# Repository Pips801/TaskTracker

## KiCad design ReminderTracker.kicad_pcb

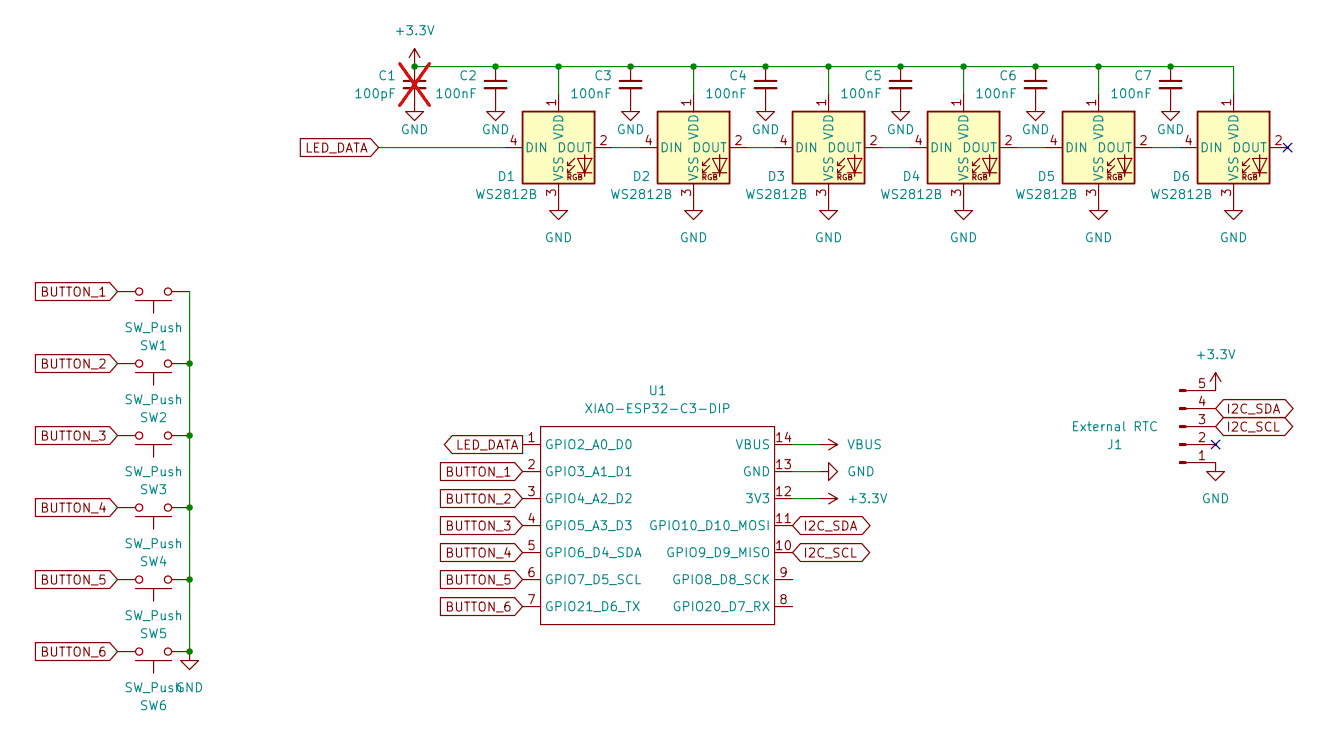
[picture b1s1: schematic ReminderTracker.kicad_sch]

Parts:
C1: 100pF; C_1206_3216Metric_Pad1.33x1.80mm_HandSolder; not fitted
C2, C3, C4, C5, C6, C7: 100nF; C_1206_3216Metric_Pad1.33x1.80mm_HandSolder
D1, D2, D3, D4, D5, D6: WS2812B; LED_WS2812B-Mini_PLCC4_3.5x3.5mm
J1: External RTC; PinHeader_1x05_P2.54mm_Vertical
SW1, SW2, SW3, SW4, SW5, SW6: SW_Push; SW_PUSH_6mm
U1: XIAO-ESP32-C3-DIP

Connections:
+3.3V: C1.1, C2.1, C3.1, C4.1, C5.1, C6.1, C7.1, D1.1 (VDD), D2.1 (VDD), D3.1 (VDD), D4.1 (VDD), D5.1 (VDD), D6.1 (VDD), J1.5, U1.12 (3V3)
BUTTON_1: SW1.2, U1.2 (GPIO3_A1_D1)
BUTTON_2: SW2.2, U1.3 (GPIO4_A2_D2)
BUTTON_3: SW3.2, U1.4 (GPIO5_A3_D3)
BUTTON_4: SW4.2, U1.5 (GPIO6_D4_SDA)
BUTTON_5: SW5.2, U1.6 (GPIO7_D5_SCL)
BUTTON_6: SW6.2, U1.7 (GPIO21_D6_TX)
GND: C1.2, C2.2, C3.2, C4.2, C5.2, C6.2, C7.2, D1.3 (VSS), D2.3 (VSS), D3.3 (VSS), D4.3 (VSS), D5.3 (VSS), D6.3 (VSS), J1.1, SW1.1, SW2.1, SW3.1, SW4.1, SW5.1, SW6.1, U1.13 (GND); also elsewhere on the board
I2C_SCL: J1.3, U1.10 (GPIO9_D9_MISO)
I2C_SDA: J1.4, U1.11 (GPIO10_D10_MOSI)
LED_DATA: D1.4 (DIN), U1.1 (GPIO2_A0_D0)
unnamed: D1.2 (DOUT), D2.4 (DIN)
unnamed: D2.2 (DOUT), D3.4 (DIN)
unnamed: D3.2 (DOUT), D4.4 (DIN)
unnamed: D4.2 (DOUT), D5.4 (DIN)
unnamed: D5.2 (DOUT), D6.4 (DIN)
VBUS: U1.14 (VBUS)

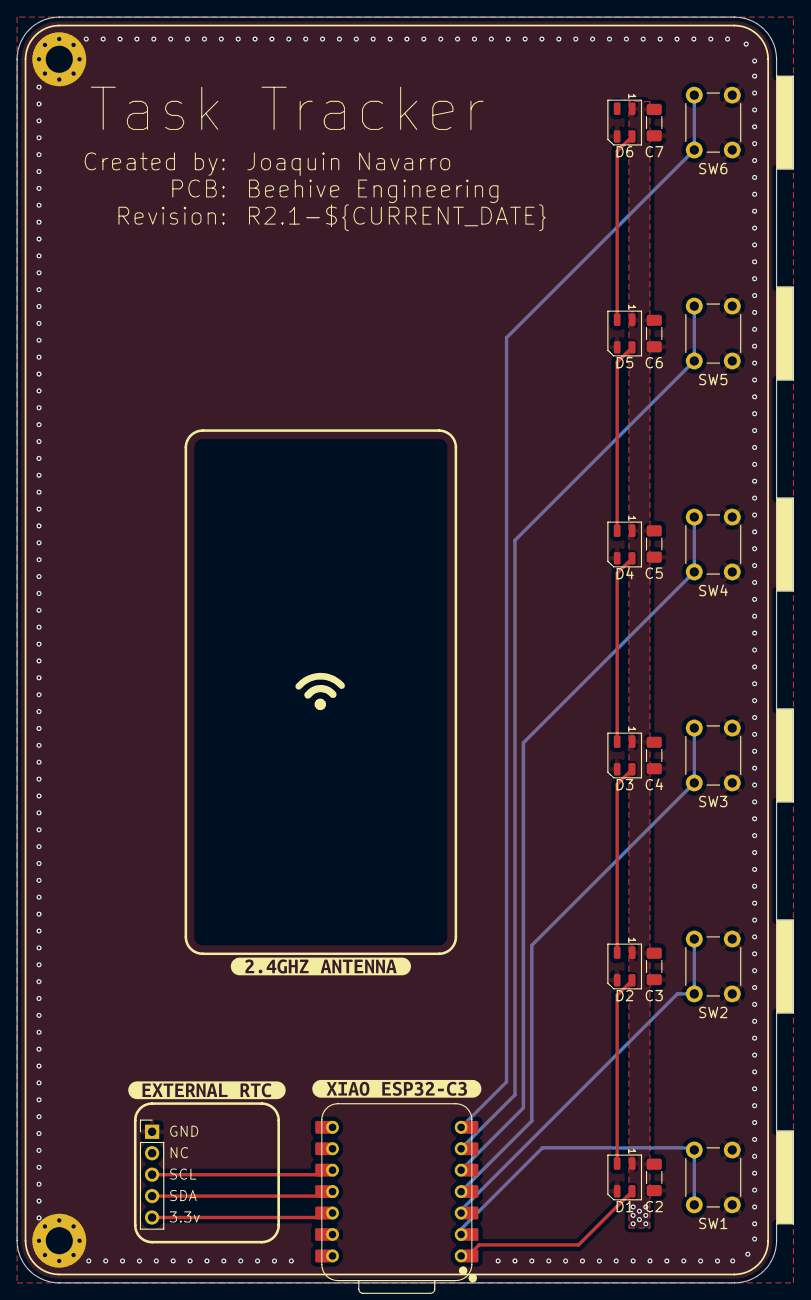
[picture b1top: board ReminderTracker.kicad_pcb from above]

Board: 2 copper layers, 92.0 x 150.0 mm, 25 parts (0 on the bottom side), 16 nets.

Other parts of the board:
H1, H2: M3; MountingHole_3.2mm_M3_Pad_Via
kibuzzard-69BB979E: G***; kibuzzard-69BB979E
kibuzzard-69BB9782: G***; kibuzzard-69BB9782
kibuzzard-69C179A5: G***; kibuzzard-69C179A5

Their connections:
GND: H1.1, H2.1; also elsewhere on the board

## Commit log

2026-03-19 1st pass
2026-03-19 fix dimensional drawings
2026-03-23 fix some things
2026-03-23 Revert "fix some things"
    This reverts commit 1e6a08e8d2bd385bda99e6b5b2198f89c5206098.
2026-03-23 R2
    Fix title
    Added antenna cutout
    Renamed to Task Tracker
2026-03-23 Antenna visual fixes
    - added silkscreen band around backside of antenna cutout
    - swapped antenna text for kiBuzzard labels
    - rounded antenna keepout and mask removal area
2026-03-23 bump revision to 2.1
2026-03-24 Update user drawings
